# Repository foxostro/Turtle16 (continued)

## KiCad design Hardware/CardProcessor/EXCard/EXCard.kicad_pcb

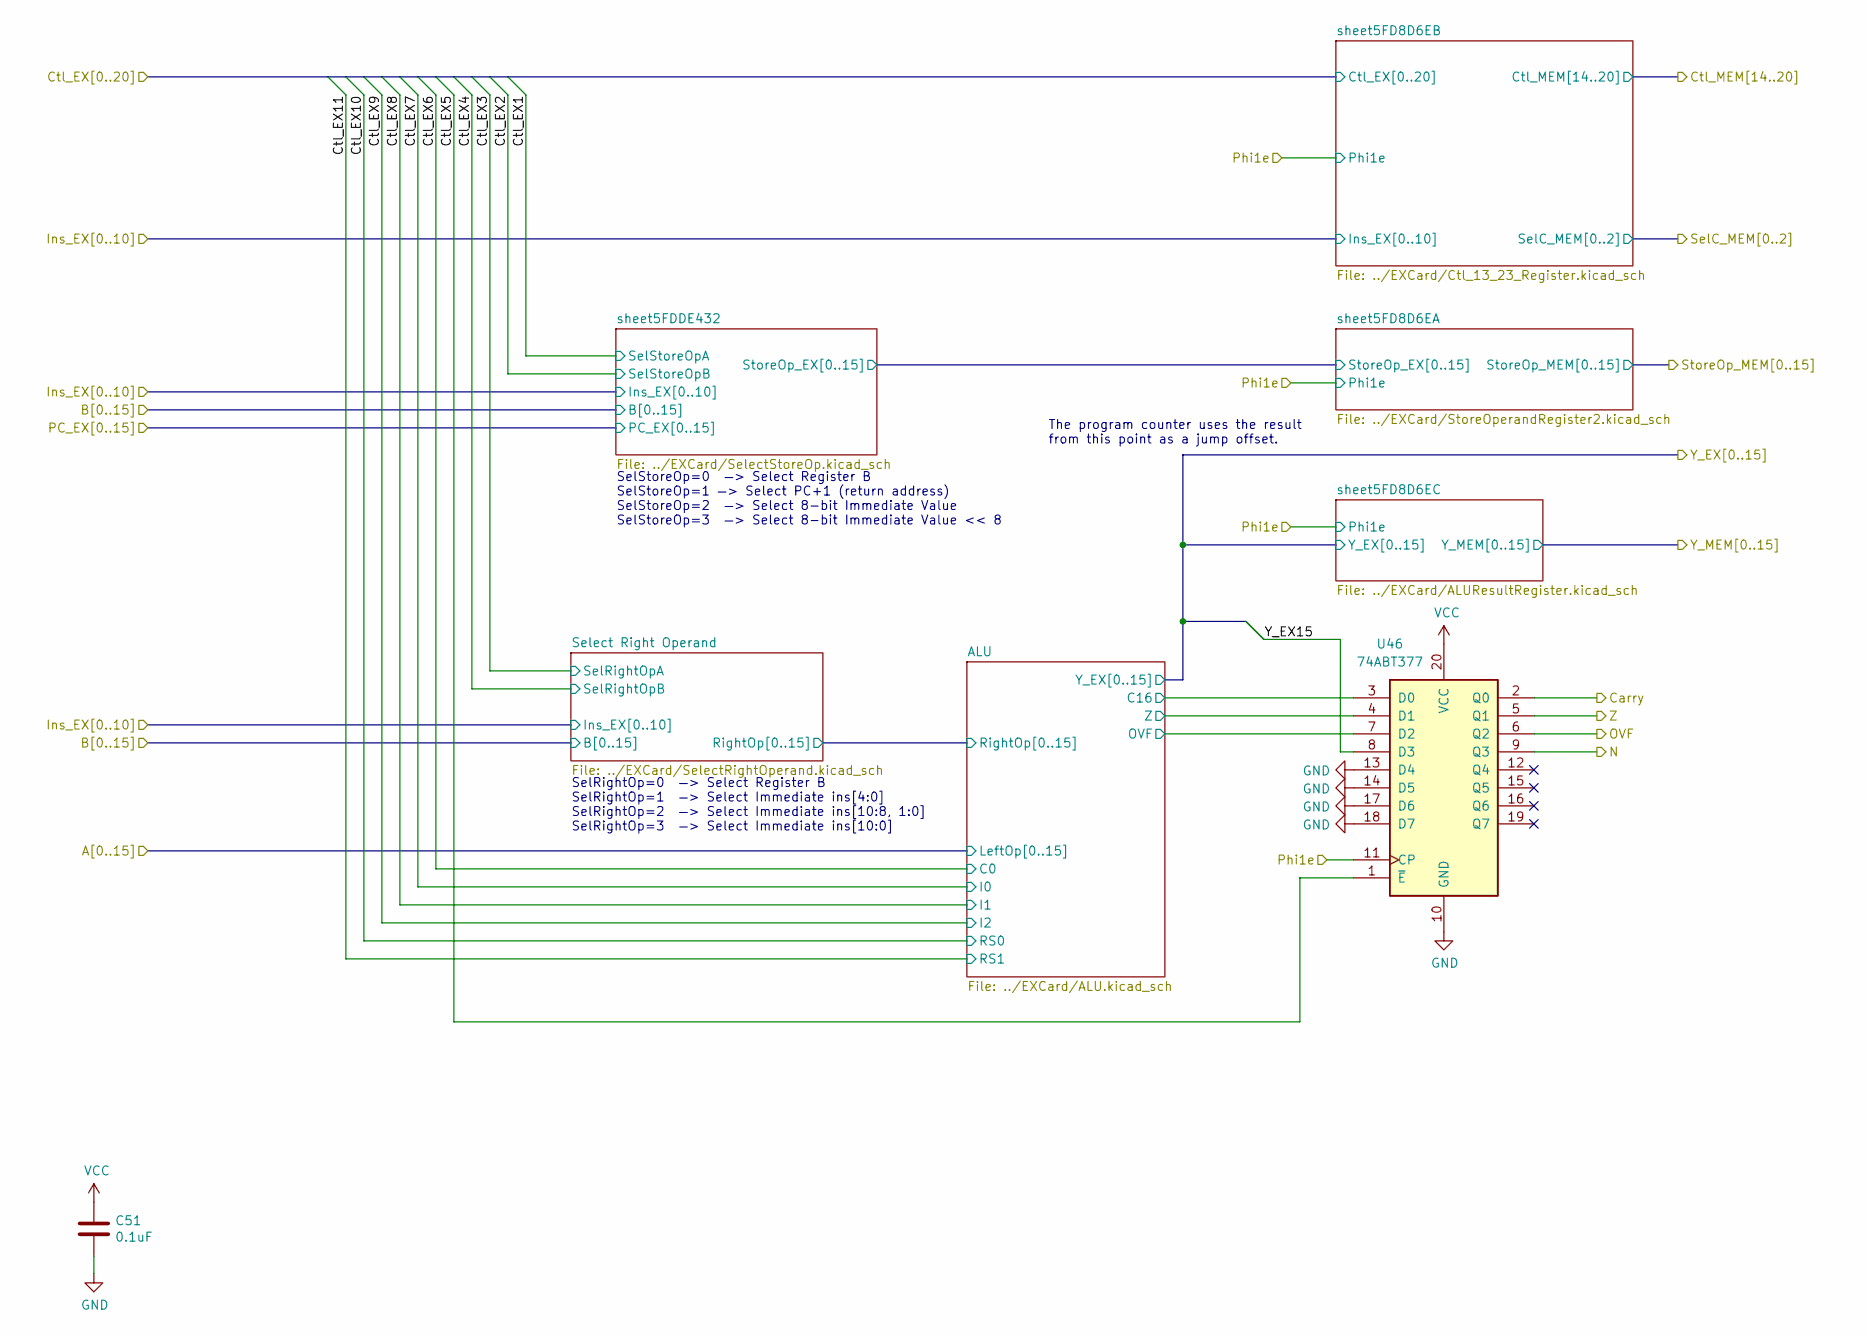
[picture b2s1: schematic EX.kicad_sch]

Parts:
C51: 0.1uF; C_0603_1608Metric; Manufacturer# EMK107B7104KAHT; Mouser# 963-EMK107B7104KAHT
U46: 74ABT377; TSSOP-20_4.4x6.5mm_P0.65mm; Manufacturer# SN74ABT377APWR; Mouser# 595-SN74ABT377APWR

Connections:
/Carry: U46.2 (Q0); also elsewhere on the board
/Ctl_EX5: U46.1 (~E); also elsewhere on the board
/EX/ALU/C16: U46.3 (D0); also elsewhere on the board
/EX/ALU/OVF: U46.7 (D2); also elsewhere on the board
/EX/ALU/Z: U46.4 (D1); also elsewhere on the board
/N: U46.9 (Q3); also elsewhere on the board
/OVF: U46.6 (Q2); also elsewhere on the board
/Phi1e: U46.11 (CP); also elsewhere on the board
/Y_EX15: U46.8 (D3); also elsewhere on the board
/Z: U46.5 (Q1); also elsewhere on the board
GND: C51.2, U46.10 (GND), U46.13 (D4), U46.14 (D5), U46.17 (D6), U46.18 (D7); also elsewhere on the board
VCC: C51.1, U46.20 (VCC); also elsewhere on the board

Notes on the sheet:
SelStoreOp=0 —> Select Register B SelStoreOp=1 —> Select PC+1 (return address) SelStoreOp=2 —> Select 8-bit Immediate Value SelStoreOp=3 —> Select 8-bit Immediate Value << 8
SelRightOp=0 —> Select Register B SelRightOp=1 —> Select Immediate ins[4:0] SelRightOp=2 —> Select Immediate ins[10:8, 1:0] SelRightOp=3 —> Select Immediate ins[10:0]
The program counter uses the result from this point as a jump offset.

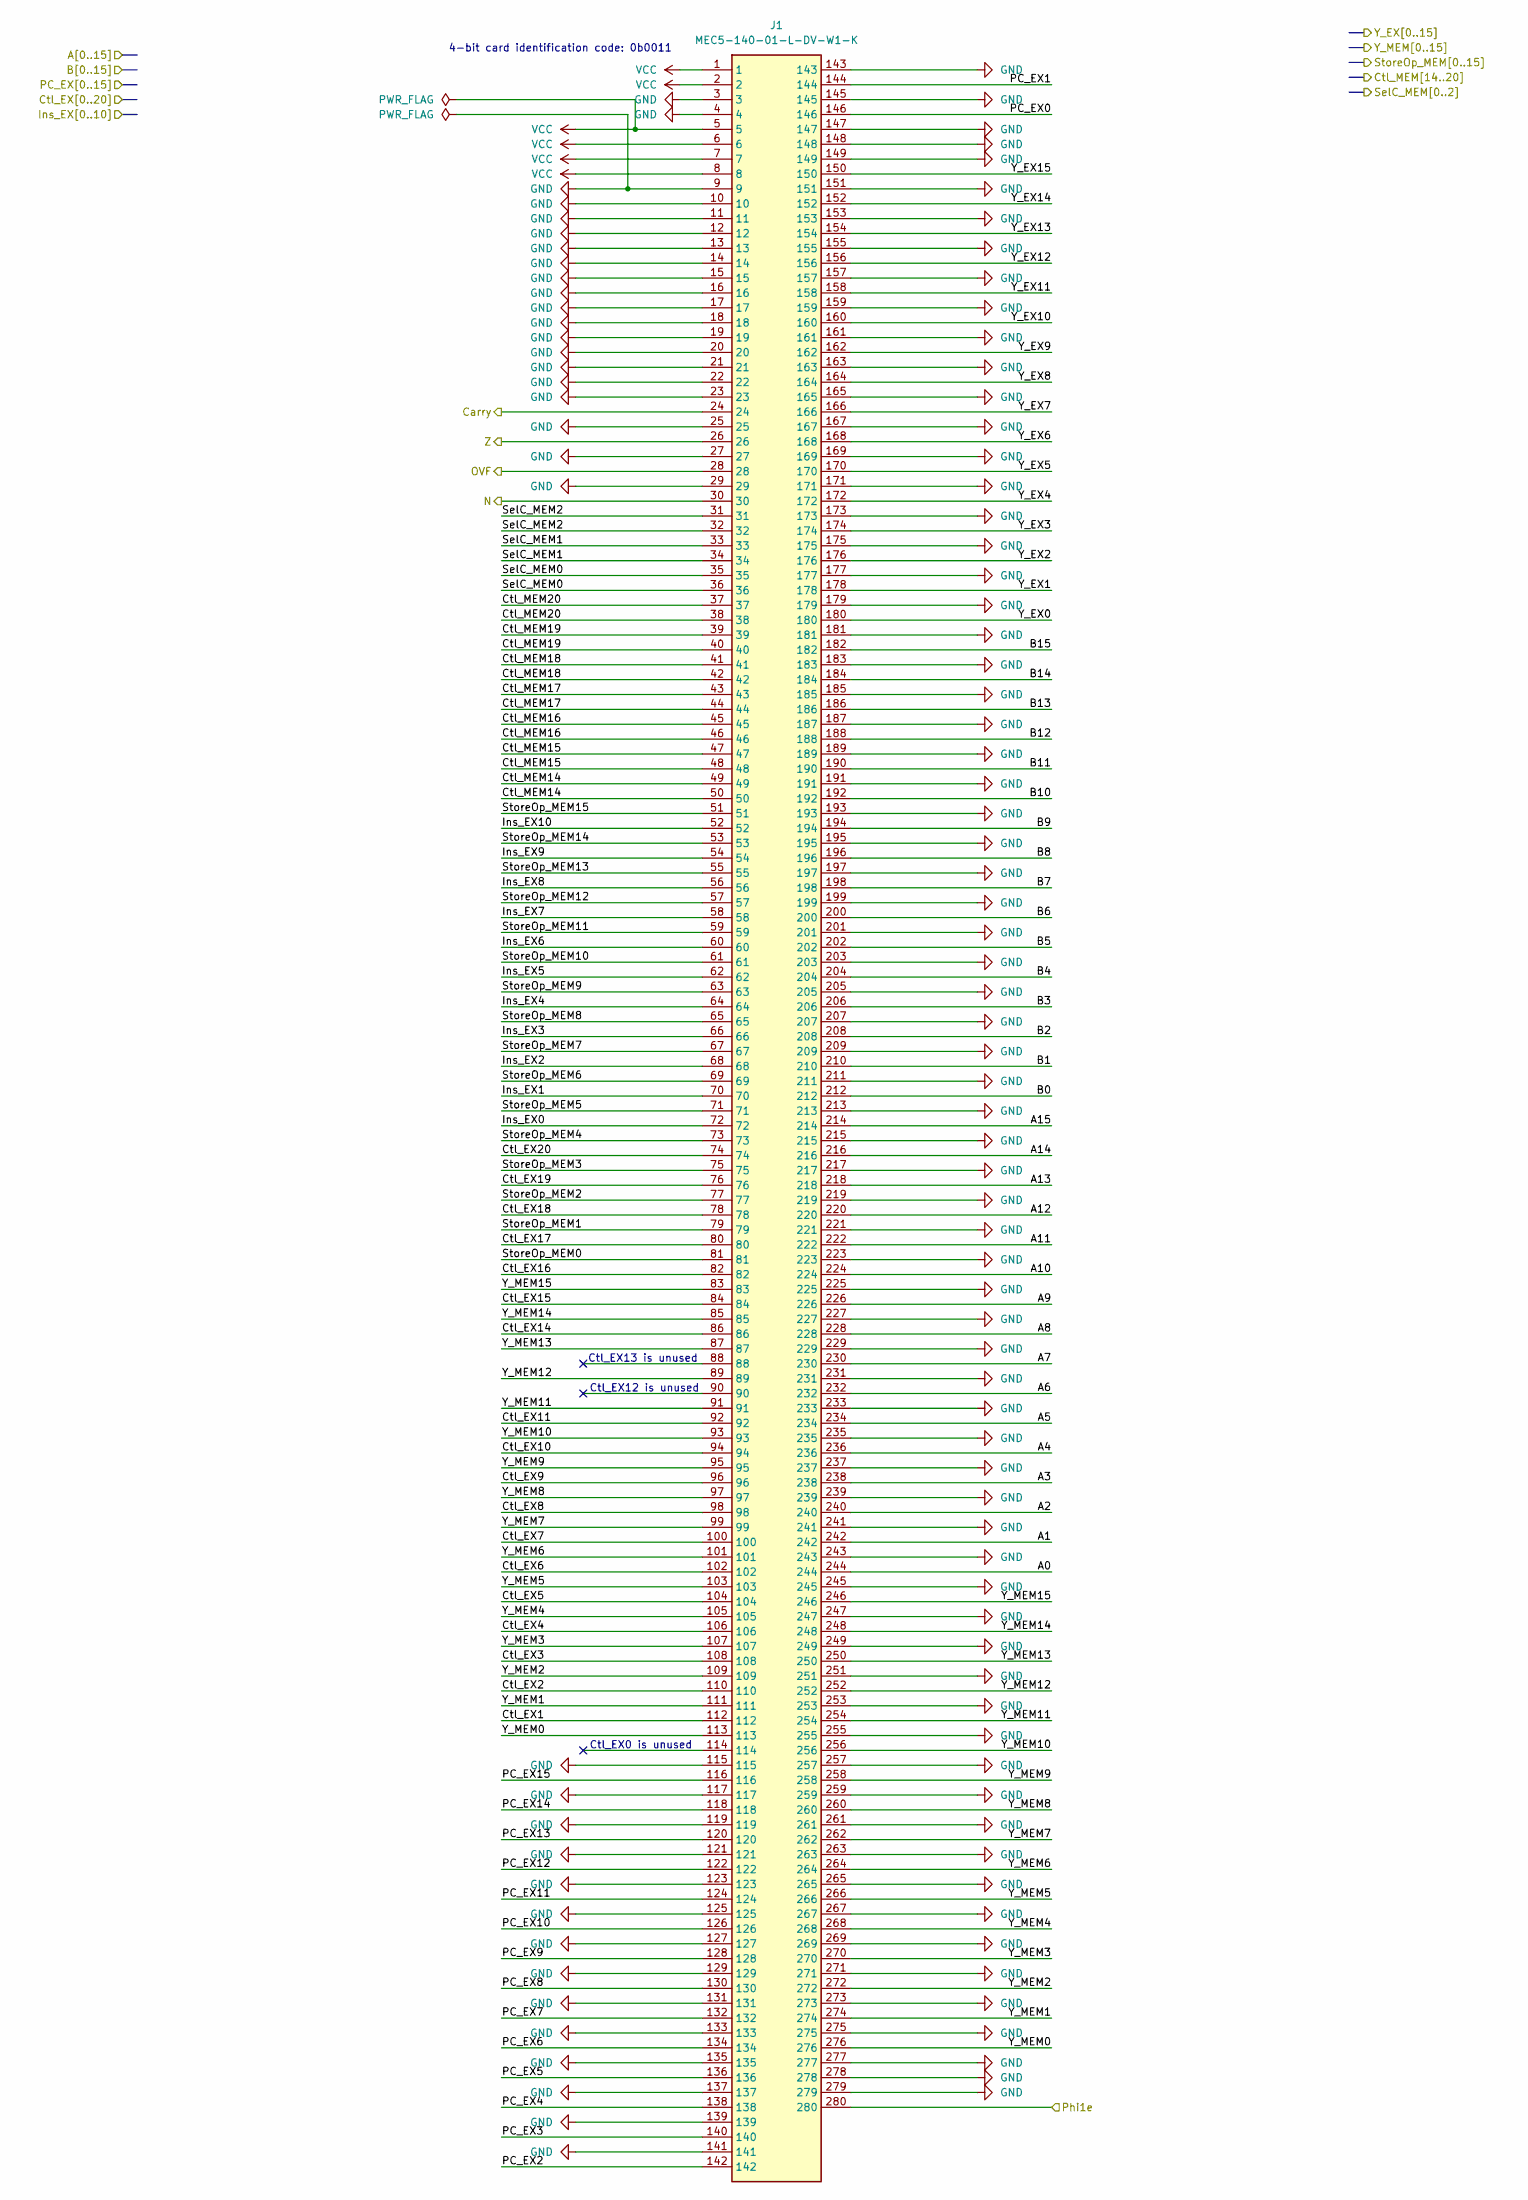
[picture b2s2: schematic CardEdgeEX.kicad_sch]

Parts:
J1: MEC5-140-01-L-DV-W1-K; MEC5-140-01-L-DV-W1-K_Edge; Mouser Part Number 200-MEC514001LDVW1K

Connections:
/A0: J1.244; also elsewhere on the board
/A1: J1.242; also elsewhere on the board
/A2: J1.240; also elsewhere on the board
/A3: J1.238; also elsewhere on the board
/A4: J1.236; also elsewhere on the board
/A5: J1.234; also elsewhere on the board
/A6: J1.232; also elsewhere on the board
/A7: J1.230; also elsewhere on the board
/A8: J1.228; also elsewhere on the board
/A9: J1.226; also elsewhere on the board
/A10: J1.224; also elsewhere on the board
/A11: J1.222; also elsewhere on the board
/A12: J1.220; also elsewhere on the board
/A13: J1.218; also elsewhere on the board
/A14: J1.216; also elsewhere on the board
/A15: J1.214; also elsewhere on the board
/B0: J1.212; also elsewhere on the board
/B1: J1.210; also elsewhere on the board
/B2: J1.208; also elsewhere on the board
/B3: J1.206; also elsewhere on the board
/B4: J1.204; also elsewhere on the board
/B5: J1.202; also elsewhere on the board
/B6: J1.200; also elsewhere on the board
/B7: J1.198; also elsewhere on the board
/B8: J1.196; also elsewhere on the board
/B9: J1.194; also elsewhere on the board
/B10: J1.192; also elsewhere on the board
/B11: J1.190; also elsewhere on the board
/B12: J1.188; also elsewhere on the board
/B13: J1.186; also elsewhere on the board
/B14: J1.184; also elsewhere on the board
/B15: J1.182; also elsewhere on the board
/Carry: J1.24; also elsewhere on the board
/Ctl_EX1: J1.112; also elsewhere on the board
/Ctl_EX2: J1.110; also elsewhere on the board
/Ctl_EX3: J1.108; also elsewhere on the board
/Ctl_EX4: J1.106; also elsewhere on the board
/Ctl_EX5: J1.104; also elsewhere on the board
/Ctl_EX6: J1.102; also elsewhere on the board
/Ctl_EX7: J1.100; also elsewhere on the board
/Ctl_EX8: J1.98; also elsewhere on the board
/Ctl_EX9: J1.96; also elsewhere on the board
/Ctl_EX10: J1.94; also elsewhere on the board
/Ctl_EX11: J1.92; also elsewhere on the board
/Ctl_EX14: J1.86; also elsewhere on the board
/Ctl_EX15: J1.84; also elsewhere on the board
/Ctl_EX16: J1.82; also elsewhere on the board
/Ctl_EX17: J1.80; also elsewhere on the board
/Ctl_EX18: J1.78; also elsewhere on the board
/Ctl_EX19: J1.76; also elsewhere on the board
/Ctl_EX20: J1.74; also elsewhere on the board
/Ctl_MEM14: J1.49, J1.50; also elsewhere on the board
/Ctl_MEM15: J1.47, J1.48; also elsewhere on the board
/Ctl_MEM16: J1.45, J1.46; also elsewhere on the board
/Ctl_MEM17: J1.43, J1.44; also elsewhere on the board
/Ctl_MEM18: J1.41, J1.42; also elsewhere on the board
/Ctl_MEM19: J1.39, J1.40; also elsewhere on the board
/Ctl_MEM20: J1.37, J1.38; also elsewhere on the board
/Ins_EX0: J1.72; also elsewhere on the board
/Ins_EX1: J1.70; also elsewhere on the board
/Ins_EX2: J1.68; also elsewhere on the board
/Ins_EX3: J1.66; also elsewhere on the board
/Ins_EX4: J1.64; also elsewhere on the board
/Ins_EX5: J1.62; also elsewhere on the board
/Ins_EX6: J1.60; also elsewhere on the board
/Ins_EX7: J1.58; also elsewhere on the board
/Ins_EX8: J1.56; also elsewhere on the board
/Ins_EX9: J1.54; also elsewhere on the board
/Ins_EX10: J1.52; also elsewhere on the board
/N: J1.30; also elsewhere on the board
/OVF: J1.28; also elsewhere on the board
/PC_EX0: J1.146; also elsewhere on the board
/PC_EX1: J1.144; also elsewhere on the board
/PC_EX2: J1.142; also elsewhere on the board
/PC_EX3: J1.140; also elsewhere on the board
/PC_EX4: J1.138; also elsewhere on the board
/PC_EX5: J1.136; also elsewhere on the board
/PC_EX6: J1.134; also elsewhere on the board
/PC_EX7: J1.132; also elsewhere on the board
/PC_EX8: J1.130; also elsewhere on the board
/PC_EX9: J1.128; also elsewhere on the board
/PC_EX10: J1.126; also elsewhere on the board
/PC_EX11: J1.124; also elsewhere on the board
/PC_EX12: J1.122; also elsewhere on the board
/PC_EX13: J1.120; also elsewhere on the board
/PC_EX14: J1.118; also elsewhere on the board
/PC_EX15: J1.116; also elsewhere on the board
/Phi1e: J1.280; also elsewhere on the board
/SelC_MEM0: J1.35, J1.36; also elsewhere on the board
/SelC_MEM1: J1.33, J1.34; also elsewhere on the board
/SelC_MEM2: J1.31, J1.32; also elsewhere on the board
/StoreOp_MEM0: J1.81; also elsewhere on the board
/StoreOp_MEM1: J1.79; also elsewhere on the board
/StoreOp_MEM2: J1.77; also elsewhere on the board
/StoreOp_MEM3: J1.75; also elsewhere on the board
/StoreOp_MEM4: J1.73; also elsewhere on the board
/StoreOp_MEM5: J1.71; also elsewhere on the board
/StoreOp_MEM6: J1.69; also elsewhere on the board
/StoreOp_MEM7: J1.67; also elsewhere on the board
/StoreOp_MEM8: J1.65; also elsewhere on the board
/StoreOp_MEM9: J1.63; also elsewhere on the board
/StoreOp_MEM10: J1.61; also elsewhere on the board
/StoreOp_MEM11: J1.59; also elsewhere on the board
/StoreOp_MEM12: J1.57; also elsewhere on the board
/StoreOp_MEM13: J1.55; also elsewhere on the board
/StoreOp_MEM14: J1.53; also elsewhere on the board
/StoreOp_MEM15: J1.51; also elsewhere on the board
/Y_EX0: J1.180; also elsewhere on the board
/Y_EX1: J1.178; also elsewhere on the board
/Y_EX2: J1.176; also elsewhere on the board
/Y_EX3: J1.174; also elsewhere on the board
/Y_EX4: J1.172; also elsewhere on the board
/Y_EX5: J1.170; also elsewhere on the board
/Y_EX6: J1.168; also elsewhere on the board
/Y_EX7: J1.166; also elsewhere on the board
/Y_EX8: J1.164; also elsewhere on the board
/Y_EX9: J1.162; also elsewhere on the board
/Y_EX10: J1.160; also elsewhere on the board
/Y_EX11: J1.158; also elsewhere on the board
/Y_EX12: J1.156; also elsewhere on the board
/Y_EX13: J1.154; also elsewhere on the board
/Y_EX14: J1.152; also elsewhere on the board
/Y_EX15: J1.150; also elsewhere on the board
/Y_MEM0: J1.113, J1.276; also elsewhere on the board
/Y_MEM1: J1.111, J1.274; also elsewhere on the board
/Y_MEM2: J1.109, J1.272; also elsewhere on the board
/Y_MEM3: J1.107, J1.270; also elsewhere on the board
/Y_MEM4: J1.105, J1.268; also elsewhere on the board
/Y_MEM5: J1.103, J1.266; also elsewhere on the board
/Y_MEM6: J1.101, J1.264; also elsewhere on the board
/Y_MEM7: J1.99, J1.262; also elsewhere on the board
/Y_MEM8: J1.97, J1.260; also elsewhere on the board
/Y_MEM9: J1.95, J1.258; also elsewhere on the board
/Y_MEM10: J1.93, J1.256; also elsewhere on the board
/Y_MEM11: J1.91, J1.254; also elsewhere on the board
/Y_MEM12: J1.89, J1.252; also elsewhere on the board
/Y_MEM13: J1.87, J1.250; also elsewhere on the board
/Y_MEM14: J1.85, J1.248; also elsewhere on the board
/Y_MEM15: J1.83, J1.246; also elsewhere on the board
/Z: J1.26; also elsewhere on the board
GND: J1.3, J1.4, J1.9, J1.10, J1.11, J1.12, J1.13, J1.14, J1.15, J1.16, J1.17, J1.18, J1.19, J1.20, J1.21, J1.22, J1.23, J1.25, J1.27, J1.29, J1.115, J1.117, J1.119, J1.121, J1.123, J1.125, J1.127, J1.129, J1.131, J1.133, J1.135, J1.137, J1.139, J1.141, J1.143, J1.145, J1.147, J1.148, J1.149, J1.151, J1.153, J1.155, J1.157, J1.159, J1.161, J1.163, J1.165, J1.167, J1.169, J1.171, J1.173, J1.175, J1.177, J1.179, J1.181, J1.183, J1.185, J1.187, J1.189, J1.191, J1.193, J1.195, J1.197, J1.199, J1.201, J1.203, J1.205, J1.207, J1.209, J1.211, J1.213, J1.215, J1.217, J1.219, J1.221, J1.223, J1.225, J1.227, J1.229, J1.231, J1.233, J1.235, J1.237, J1.239, J1.241, J1.243, J1.245, J1.247, J1.249, J1.251, J1.253, J1.255, J1.257, J1.259, J1.261, J1.263, J1.265, J1.267, J1.269, J1.271, J1.273, J1.275, J1.277, J1.278, J1.279; also elsewhere on the board
VCC: J1.1, J1.2, J1.5, J1.6, J1.7, J1.8; also elsewhere on the board

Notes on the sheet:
4-bit card identification code: 0b0011
Ctl_EX13 is unused
Ctl_EX0 is unused
Ctl_EX12 is unused

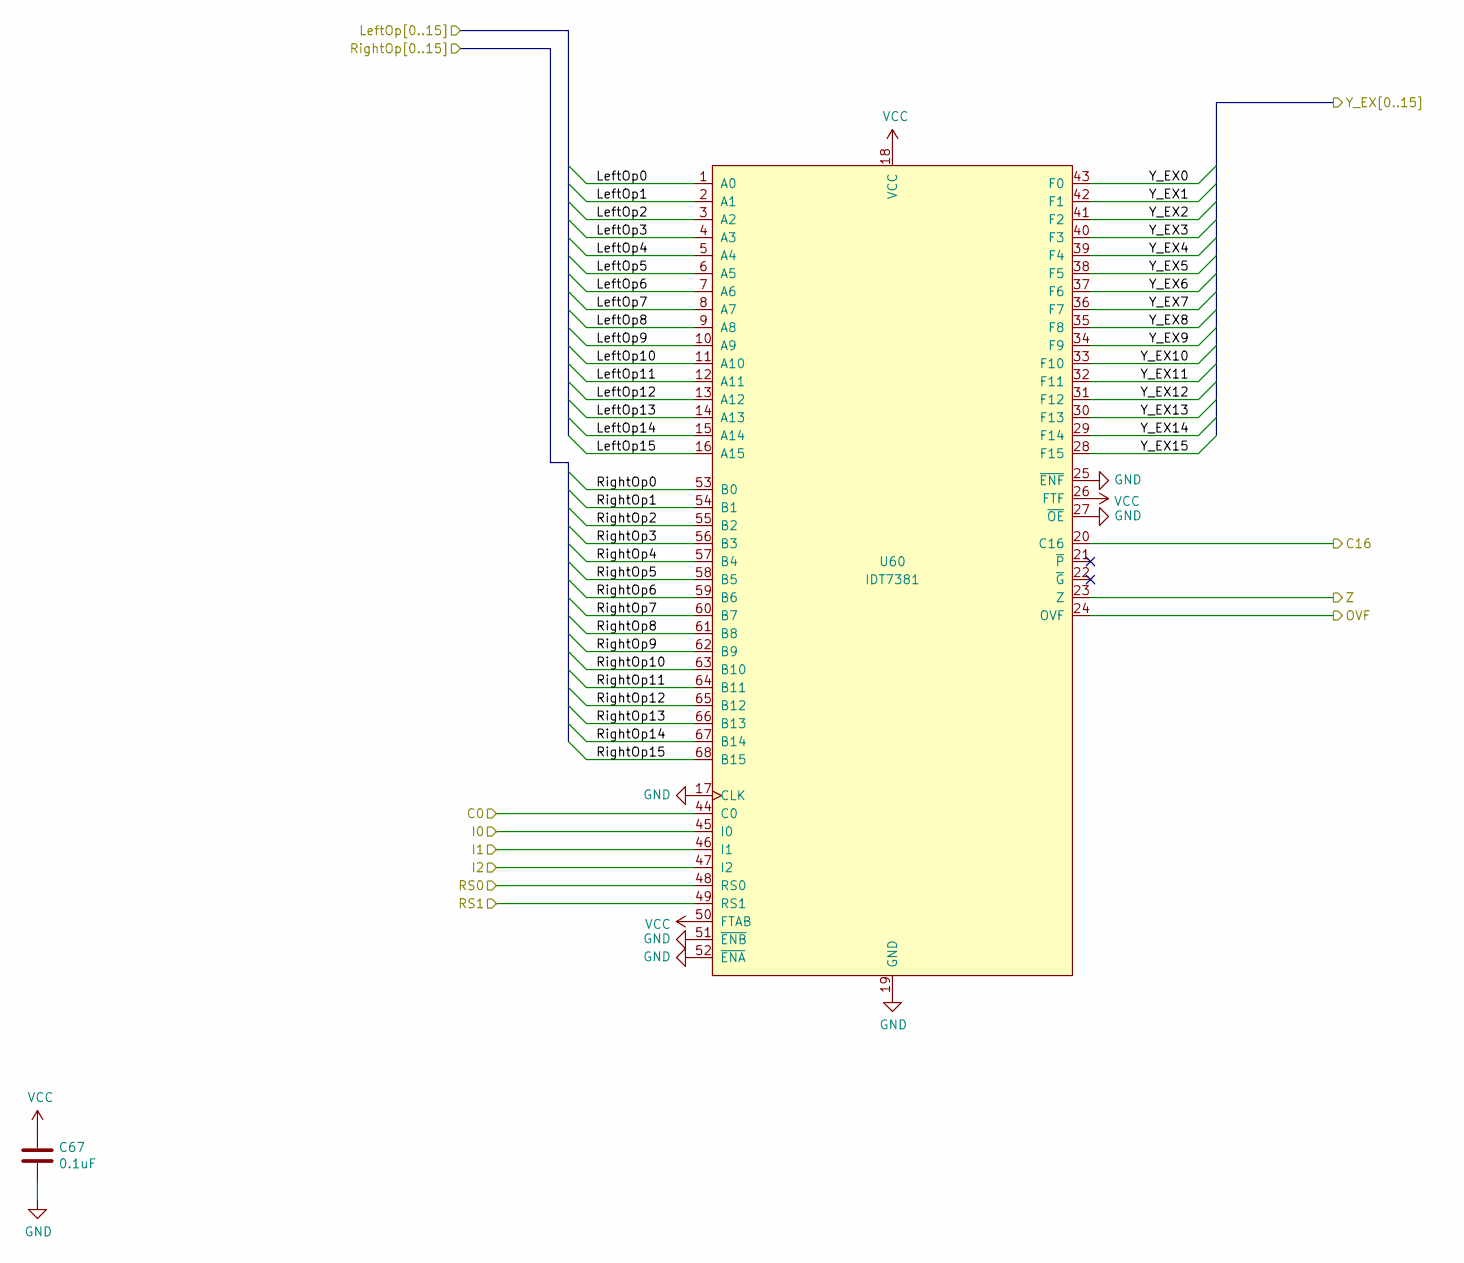
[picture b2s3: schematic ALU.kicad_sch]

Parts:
C67: 0.1uF; C_0603_1608Metric; Manufacturer# EMK107B7104KAHT; Mouser# 963-EMK107B7104KAHT
U60: IDT7381; PLCC-68_SMD-Socket; Manufacturer# 8468-21B1-RK-TP; Mouser# 517-8468-21B1-RK-TP

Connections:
/A0: U60.1 (A0); also elsewhere on the board
/A1: U60.2 (A1); also elsewhere on the board
/A2: U60.3 (A2); also elsewhere on the board
/A3: U60.4 (A3); also elsewhere on the board
/A4: U60.5 (A4); also elsewhere on the board
/A5: U60.6 (A5); also elsewhere on the board
/A6: U60.7 (A6); also elsewhere on the board
/A7: U60.8 (A7); also elsewhere on the board
/A8: U60.9 (A8); also elsewhere on the board
/A9: U60.10 (A9); also elsewhere on the board
/A10: U60.11 (A10); also elsewhere on the board
/A11: U60.12 (A11); also elsewhere on the board
/A12: U60.13 (A12); also elsewhere on the board
/A13: U60.14 (A13); also elsewhere on the board
/A14: U60.15 (A14); also elsewhere on the board
/A15: U60.16 (A15); also elsewhere on the board
/Ctl_EX6: U60.44 (C0); also elsewhere on the board
/Ctl_EX7: U60.45 (I0); also elsewhere on the board
/Ctl_EX8: U60.46 (I1); also elsewhere on the board
/Ctl_EX9: U60.47 (I2); also elsewhere on the board
/Ctl_EX10: U60.48 (RS0); also elsewhere on the board
/Ctl_EX11: U60.49 (RS1); also elsewhere on the board
/EX/ALU/C16: U60.20 (C16); also elsewhere on the board
/EX/ALU/OVF: U60.24 (OVF); also elsewhere on the board
/EX/ALU/RightOp0: U60.53 (B0); also elsewhere on the board
/EX/ALU/RightOp1: U60.54 (B1); also elsewhere on the board
/EX/ALU/RightOp2: U60.55 (B2); also elsewhere on the board
/EX/ALU/RightOp3: U60.56 (B3); also elsewhere on the board
/EX/ALU/RightOp4: U60.57 (B4); also elsewhere on the board
/EX/ALU/RightOp5: U60.58 (B5); also elsewhere on the board
/EX/ALU/RightOp6: U60.59 (B6); also elsewhere on the board
/EX/ALU/RightOp7: U60.60 (B7); also elsewhere on the board
/EX/ALU/RightOp8: U60.61 (B8); also elsewhere on the board
/EX/ALU/RightOp9: U60.62 (B9); also elsewhere on the board
/EX/ALU/RightOp10: U60.63 (B10); also elsewhere on the board
/EX/ALU/RightOp11: U60.64 (B11); also elsewhere on the board
/EX/ALU/RightOp12: U60.65 (B12); also elsewhere on the board
/EX/ALU/RightOp13: U60.66 (B13); also elsewhere on the board
/EX/ALU/RightOp14: U60.67 (B14); also elsewhere on the board
/EX/ALU/RightOp15: U60.68 (B15); also elsewhere on the board
/EX/ALU/Z: U60.23 (Z); also elsewhere on the board
/Y_EX0: U60.43 (F0); also elsewhere on the board
/Y_EX1: U60.42 (F1); also elsewhere on the board
/Y_EX2: U60.41 (F2); also elsewhere on the board
/Y_EX3: U60.40 (F3); also elsewhere on the board
/Y_EX4: U60.39 (F4); also elsewhere on the board
/Y_EX5: U60.38 (F5); also elsewhere on the board
/Y_EX6: U60.37 (F6); also elsewhere on the board
/Y_EX7: U60.36 (F7); also elsewhere on the board
/Y_EX8: U60.35 (F8); also elsewhere on the board
/Y_EX9: U60.34 (F9); also elsewhere on the board
/Y_EX10: U60.33 (F10); also elsewhere on the board
/Y_EX11: U60.32 (F11); also elsewhere on the board
/Y_EX12: U60.31 (F12); also elsewhere on the board
/Y_EX13: U60.30 (F13); also elsewhere on the board
/Y_EX14: U60.29 (F14); also elsewhere on the board
/Y_EX15: U60.28 (F15); also elsewhere on the board
GND: C67.2, U60.17 (CLK), U60.19 (GND), U60.25 (~ENF), U60.27 (~OE), U60.51 (~ENB), U60.52 (~ENA); also elsewhere on the board
VCC: C67.1, U60.18 (VCC), U60.26 (FTF), U60.50 (FTAB); also elsewhere on the board

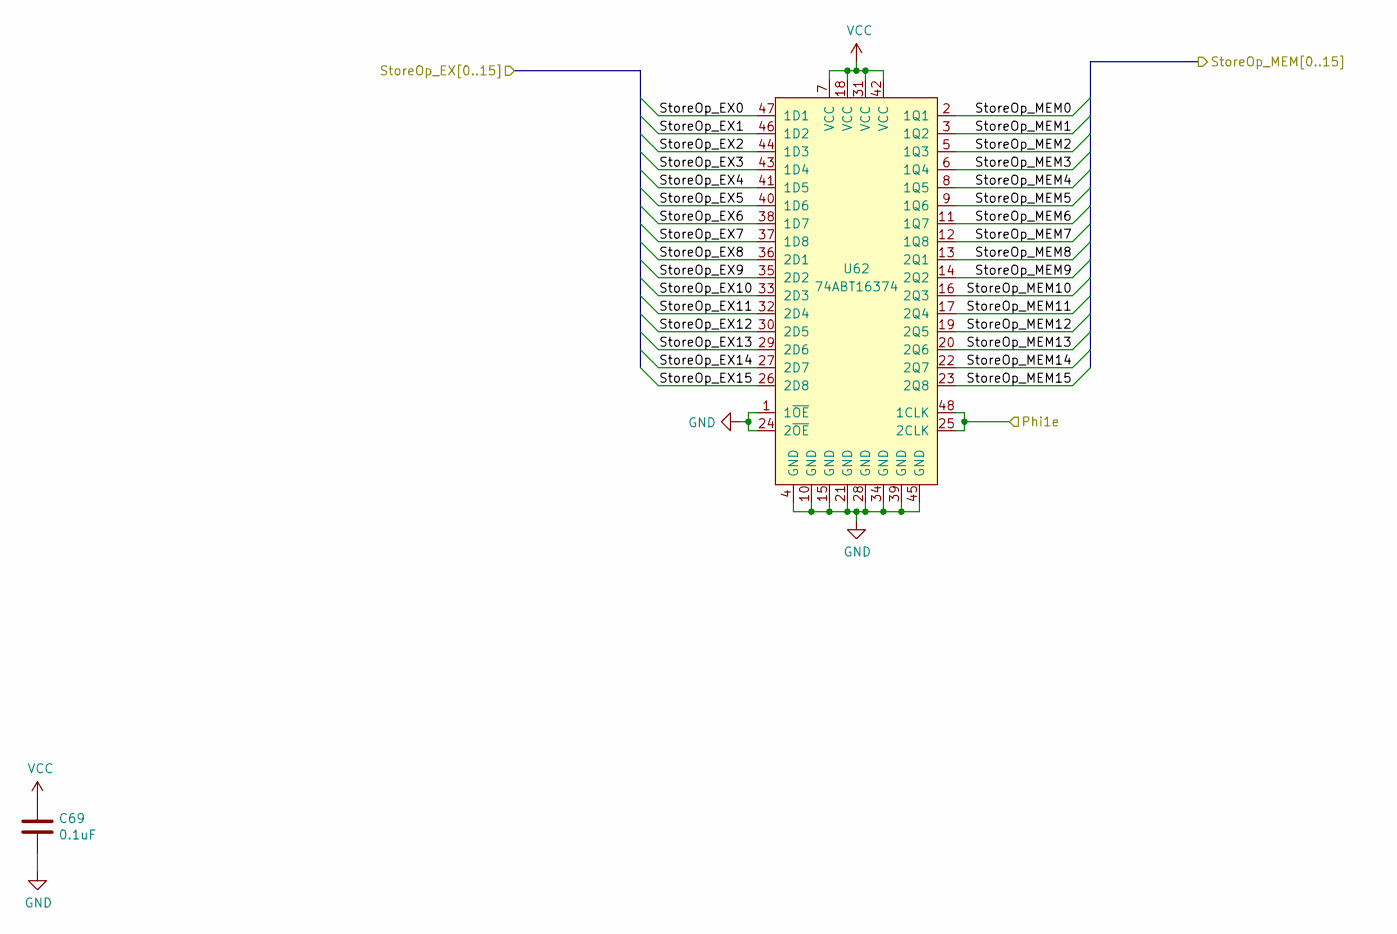
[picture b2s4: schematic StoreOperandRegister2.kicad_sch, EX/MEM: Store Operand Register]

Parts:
C69: 0.1uF; C_0603_1608Metric; Manufacturer# EMK107B7104KAHT; Mouser# 963-EMK107B7104KAHT
U62: 74ABT16374; TSSOP-48_6.1x12.5mm_P0.5mm; Manufacturer# SN74ABT16374ADGGR; Mouser# 595-SNABT16374ADGGR

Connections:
/EX/sheet5FD8D6EA/StoreOp_EX0: U62.47 (1D1); also elsewhere on the board
/EX/sheet5FD8D6EA/StoreOp_EX1: U62.46 (1D2); also elsewhere on the board
/EX/sheet5FD8D6EA/StoreOp_EX2: U62.44 (1D3); also elsewhere on the board
/EX/sheet5FD8D6EA/StoreOp_EX3: U62.43 (1D4); also elsewhere on the board
/EX/sheet5FD8D6EA/StoreOp_EX4: U62.41 (1D5); also elsewhere on the board
/EX/sheet5FD8D6EA/StoreOp_EX5: U62.40 (1D6); also elsewhere on the board
/EX/sheet5FD8D6EA/StoreOp_EX6: U62.38 (1D7); also elsewhere on the board
/EX/sheet5FD8D6EA/StoreOp_EX7: U62.37 (1D8); also elsewhere on the board
/EX/sheet5FD8D6EA/StoreOp_EX8: U62.36 (2D1); also elsewhere on the board
/EX/sheet5FD8D6EA/StoreOp_EX9: U62.35 (2D2); also elsewhere on the board
/EX/sheet5FD8D6EA/StoreOp_EX10: U62.33 (2D3); also elsewhere on the board
/EX/sheet5FD8D6EA/StoreOp_EX11: U62.32 (2D4); also elsewhere on the board
/EX/sheet5FD8D6EA/StoreOp_EX12: U62.30 (2D5); also elsewhere on the board
/EX/sheet5FD8D6EA/StoreOp_EX13: U62.29 (2D6); also elsewhere on the board
/EX/sheet5FD8D6EA/StoreOp_EX14: U62.27 (2D7); also elsewhere on the board
/EX/sheet5FD8D6EA/StoreOp_EX15: U62.26 (2D8); also elsewhere on the board
/Phi1e: U62.25 (2CLK), U62.48 (1CLK); also elsewhere on the board
/StoreOp_MEM0: U62.2 (1Q1); also elsewhere on the board
/StoreOp_MEM1: U62.3 (1Q2); also elsewhere on the board
/StoreOp_MEM2: U62.5 (1Q3); also elsewhere on the board
/StoreOp_MEM3: U62.6 (1Q4); also elsewhere on the board
/StoreOp_MEM4: U62.8 (1Q5); also elsewhere on the board
/StoreOp_MEM5: U62.9 (1Q6); also elsewhere on the board
/StoreOp_MEM6: U62.11 (1Q7); also elsewhere on the board
/StoreOp_MEM7: U62.12 (1Q8); also elsewhere on the board
/StoreOp_MEM8: U62.13 (2Q1); also elsewhere on the board
/StoreOp_MEM9: U62.14 (2Q2); also elsewhere on the board
/StoreOp_MEM10: U62.16 (2Q3); also elsewhere on the board
/StoreOp_MEM11: U62.17 (2Q4); also elsewhere on the board
/StoreOp_MEM12: U62.19 (2Q5); also elsewhere on the board
/StoreOp_MEM13: U62.20 (2Q6); also elsewhere on the board
/StoreOp_MEM14: U62.22 (2Q7); also elsewhere on the board
/StoreOp_MEM15: U62.23 (2Q8); also elsewhere on the board
GND: C69.2, U62.1 (1~OE), U62.4 (GND), U62.10 (GND), U62.15 (GND), U62.21 (GND), U62.24 (2~OE), U62.28 (GND), U62.34 (GND), U62.39 (GND), U62.45 (GND); also elsewhere on the board
VCC: C69.1, U62.7 (VCC), U62.18 (VCC), U62.31 (VCC), U62.42 (VCC); also elsewhere on the board

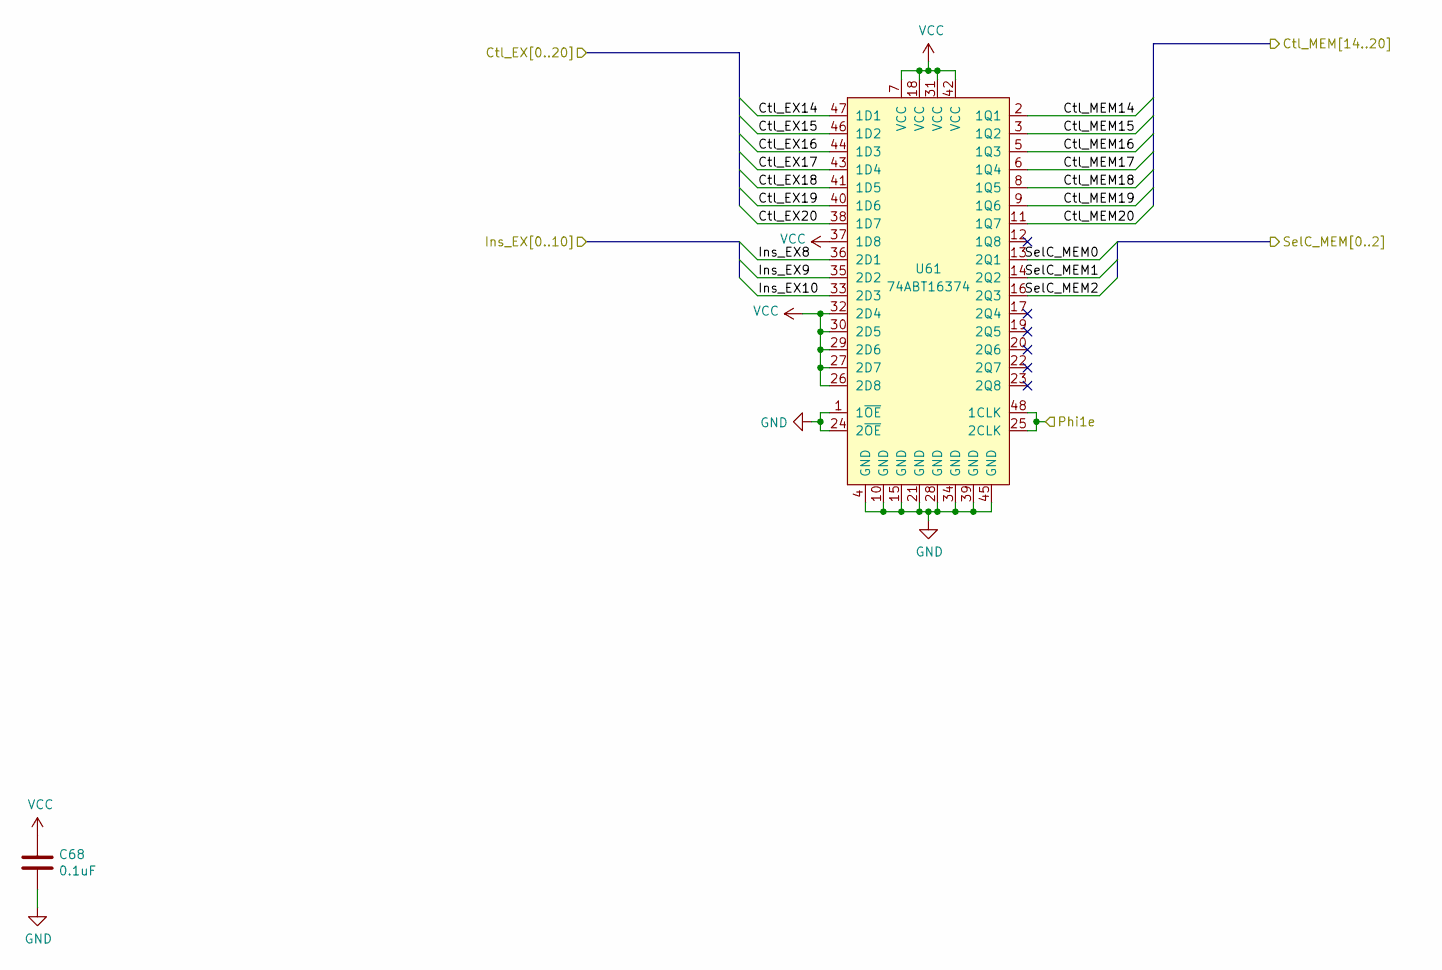
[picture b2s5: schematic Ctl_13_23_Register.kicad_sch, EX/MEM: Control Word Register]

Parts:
C68: 0.1uF; C_0603_1608Metric; Manufacturer# EMK107B7104KAHT; Mouser# 963-EMK107B7104KAHT
U61: 74ABT16374; TSSOP-48_6.1x12.5mm_P0.5mm; Manufacturer# SN74ABT16374ADGGR; Mouser# 595-SNABT16374ADGGR

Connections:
/Ctl_EX14: U61.47 (1D1); also elsewhere on the board
/Ctl_EX15: U61.46 (1D2); also elsewhere on the board
/Ctl_EX16: U61.44 (1D3); also elsewhere on the board
/Ctl_EX17: U61.43 (1D4); also elsewhere on the board
/Ctl_EX18: U61.41 (1D5); also elsewhere on the board
/Ctl_EX19: U61.40 (1D6); also elsewhere on the board
/Ctl_EX20: U61.38 (1D7); also elsewhere on the board
/Ctl_MEM14: U61.2 (1Q1); also elsewhere on the board
/Ctl_MEM15: U61.3 (1Q2); also elsewhere on the board
/Ctl_MEM16: U61.5 (1Q3); also elsewhere on the board
/Ctl_MEM17: U61.6 (1Q4); also elsewhere on the board
/Ctl_MEM18: U61.8 (1Q5); also elsewhere on the board
/Ctl_MEM19: U61.9 (1Q6); also elsewhere on the board
/Ctl_MEM20: U61.11 (1Q7); also elsewhere on the board
/Ins_EX8: U61.36 (2D1); also elsewhere on the board
/Ins_EX9: U61.35 (2D2); also elsewhere on the board
/Ins_EX10: U61.33 (2D3); also elsewhere on the board
/Phi1e: U61.25 (2CLK), U61.48 (1CLK); also elsewhere on the board
/SelC_MEM0: U61.13 (2Q1); also elsewhere on the board
/SelC_MEM1: U61.14 (2Q2); also elsewhere on the board
/SelC_MEM2: U61.16 (2Q3); also elsewhere on the board
GND: C68.2, U61.1 (1~OE), U61.4 (GND), U61.10 (GND), U61.15 (GND), U61.21 (GND), U61.24 (2~OE), U61.28 (GND), U61.34 (GND), U61.39 (GND), U61.45 (GND); also elsewhere on the board
VCC: C68.1, U61.7 (VCC), U61.18 (VCC), U61.26 (2D8), U61.27 (2D7), U61.29 (2D6), U61.30 (2D5), U61.31 (VCC), U61.32 (2D4), U61.37 (1D8), U61.42 (VCC); also elsewhere on the board
